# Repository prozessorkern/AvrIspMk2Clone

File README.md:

# Development Tools
In this repo there will be some development tools that can be used to work on some kind of hard and software projects...

## AvrIspMk2Clone
Clone of an AvrIspMk2 based on the work of http://www.ullihome.de/wiki/USBAVRLab/index

## jtagTc2050Adaptor
Adaptor PCB to connect a Tag Connect TC2050 10 Pin Needle adaptor to a standard 20 Pin JTAG Debugger
There are some additional tools integrated like a USB-UART Converter which can be connected to the TC2050 by setting Jumpers...

## pcbList
A Listing of all of my designed pcbs to find the data of a pcb a little bit faster...

## storageSolutions
Here are some sources to build systems to help storing and using components

### smdDispenser
This is something that I thought of to store and get my 0603 and 0805 smd parts (on smd rolls)
There are drawings you can use on a CNC machine... (wood, plastic and aluminium)
In addition you will need some Parts...

### smdStorage
Some drawings of inlays to store shorte SMD Strips 0603/0805 and bigger...

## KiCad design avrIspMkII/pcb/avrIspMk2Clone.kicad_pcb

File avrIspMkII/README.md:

# AvrIspMk2Clone
Clone of an AvrIspMk2 based on the work of http://www.ullihome.de/wiki/USBAVRLab/index

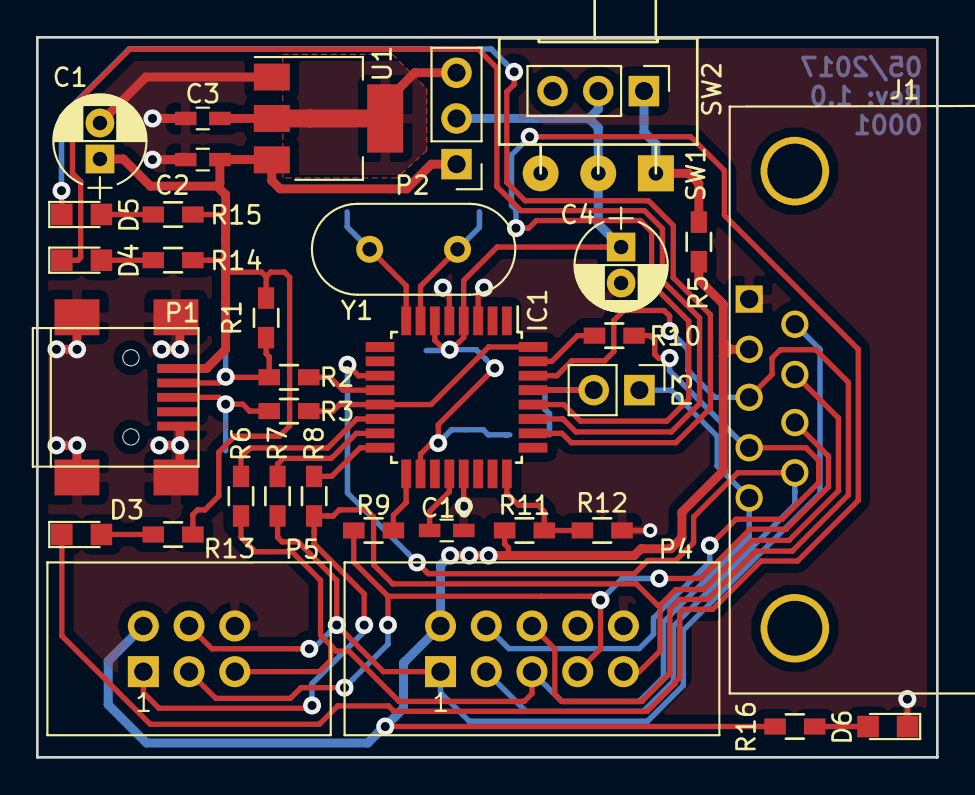
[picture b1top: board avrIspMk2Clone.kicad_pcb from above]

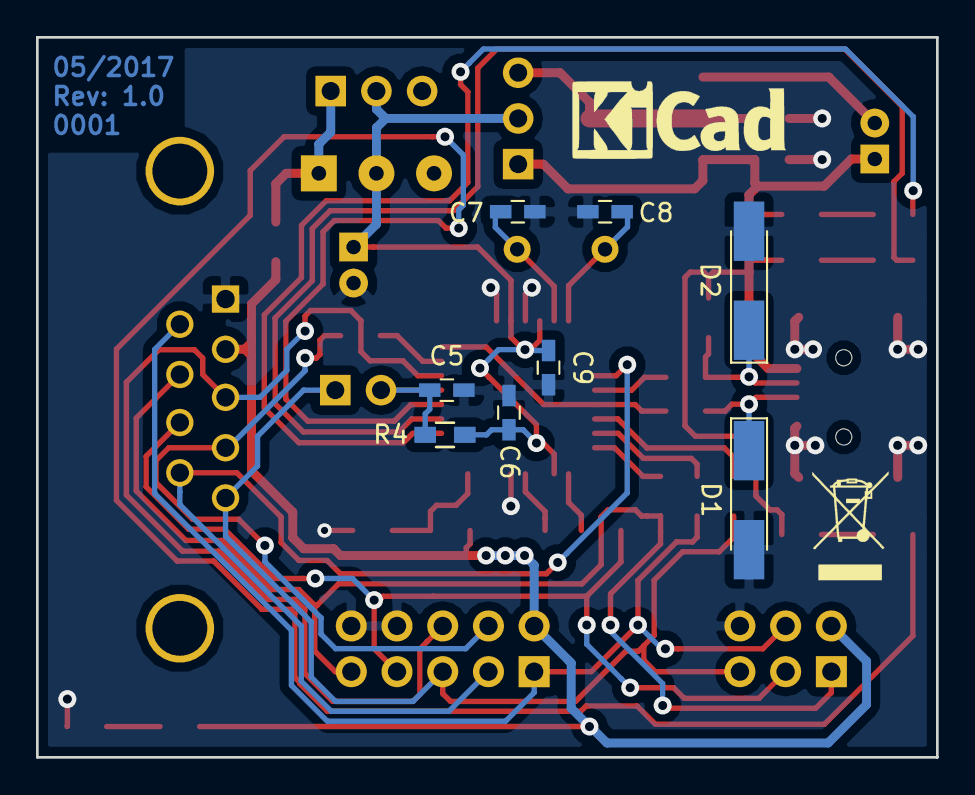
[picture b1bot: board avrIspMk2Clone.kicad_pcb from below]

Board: 2 copper layers, 50.0 x 40.0 mm, 43 parts (8 on the bottom side), 34 nets.

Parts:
C1, C4: 47u; CP_Radial_D5.0mm_P2.00mm
C2, C3, C5, C6, C9, C10: 100n; C_0603_HandSoldering
C7, C8: 22p; C_0603_HandSoldering
D1, D2: 3V3; D_MiniMELF_Handsoldering
D3, D6: BLUE; LED_0805
D4: RED; LED_0805
D5: GREEN; LED_0805
IC1: ATMEGA8-16AU; TQFP-32_7x7mm_Pitch0.8mm
J1: DB9; DB9FC
P1: USB_OTG; USB_Mini-B
P2: CONN_01X03; Pin_Header_Straight_1x03_Pitch2.54mm
P3: CONN_01X02; Pin_Header_Straight_1x02_Pitch2.54mm
P4: CONN_02X05; IDC_Header_Straight_10pins
P5: CONN_02X03; IDC_Header_Straight_6pins
R1: 2k2; R_0603_HandSoldering
R2, R3: 39; R_0603_HandSoldering
R4, R12: 10k; R_0603_HandSoldering
R5: 1; R_0603_HandSoldering
R6, R7, R8, R9: 100; R_0603_HandSoldering
R10, R13, R14, R15, R16: 1k; R_0603_HandSoldering
R11: 22k; R_0603_HandSoldering
SW1: SW_SPDT; SW_Micro_Slide_3.8
SW2: SW_SPDT; Pin_Header_Straight_1x03_Pitch2.54mm
U1: LM1117-3.3; SOT-223
Y1: 12MHz; Crystal_HC49-U_Vertical

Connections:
+3V3: C3.1, P2.3, U1.2, U1.4
+5V: C1.1, C2.1, P1.1, P2.1, R1.2, R13.2, R14.2, R15.2, U1.3
/AVREF: C10.1, IC1.20
/LED_BLUE: D3.1, IC1.28
/LED_GREEN: D5.1, IC1.26
/LED_RED: D4.1, IC1.27
/MEASURE: IC1.24, R11.1, R12.2
/MISO_OUT: J1.7, P4.9, P5.1, R8.2
/MOSI_OUT: J1.6, P4.1, P5.4, R7.2
/RESET: C5.1, IC1.29, P3.2, R4.1
/RESET_OUT: J1.5, P3.1, P4.5, P5.5, R6.2
/RXD_OUT: IC1.30, J1.3, P4.6
/SCK_OUT: J1.8, P4.7, P5.3, R9.2
/TXD_OUT: J1.4, P4.4, R10.1
/USB_D_+: IC1.13, IC1.32, R3.1
/USB_D_-: IC1.12, R2.1
/USIG1: IC1.11, J1.9, P4.3
/VCC_OUT: J1.2, P4.2, P5.2, R5.2, R11.2, R16.2
GND: C1.2, C2.2, C3.2, C4.2, C5.2, C6.2, C7.2, C8.2, C9.2, C10.2, D1.2, D2.2, D6.1, IC1.3, IC1.5, IC1.21, J1.1, P1.5, P1.6, P4.8, P4.10, P5.6, R12.1, U1.1
unnamed: C7.1, IC1.7, Y1.1
unnamed: C8.1, IC1.8, Y1.2
unnamed: D1.1, P1.3, R3.2
unnamed: D2.1, P1.2, R1.1, R2.2
unnamed: D3.2, R13.1
unnamed: D4.2, R14.1
unnamed: D5.2, R15.1
unnamed: D6.2, R16.1
unnamed: IC1.14, R6.1
unnamed: IC1.15, R7.1
unnamed: IC1.16, R8.1
unnamed: IC1.17, R9.1
unnamed: IC1.31, R10.2
unnamed: R5.1, SW1.1, SW2.1
VCC: C4.1, C6.1, C9.1, IC1.4, IC1.6, IC1.18, P2.2, R4.2, SW1.2, SW2.2

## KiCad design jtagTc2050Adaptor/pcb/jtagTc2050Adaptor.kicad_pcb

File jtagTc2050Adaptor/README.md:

# jtagTc2050Adaptor
Adaptor PCB to connect a Tag Connect TC2050 10 Pin Needle adaptor to a standard 20 Pin JTAG Debugger
There are some additional tools integrated like a USB-UART Converter which can be connected to the TC2050 by setting Jumpers...

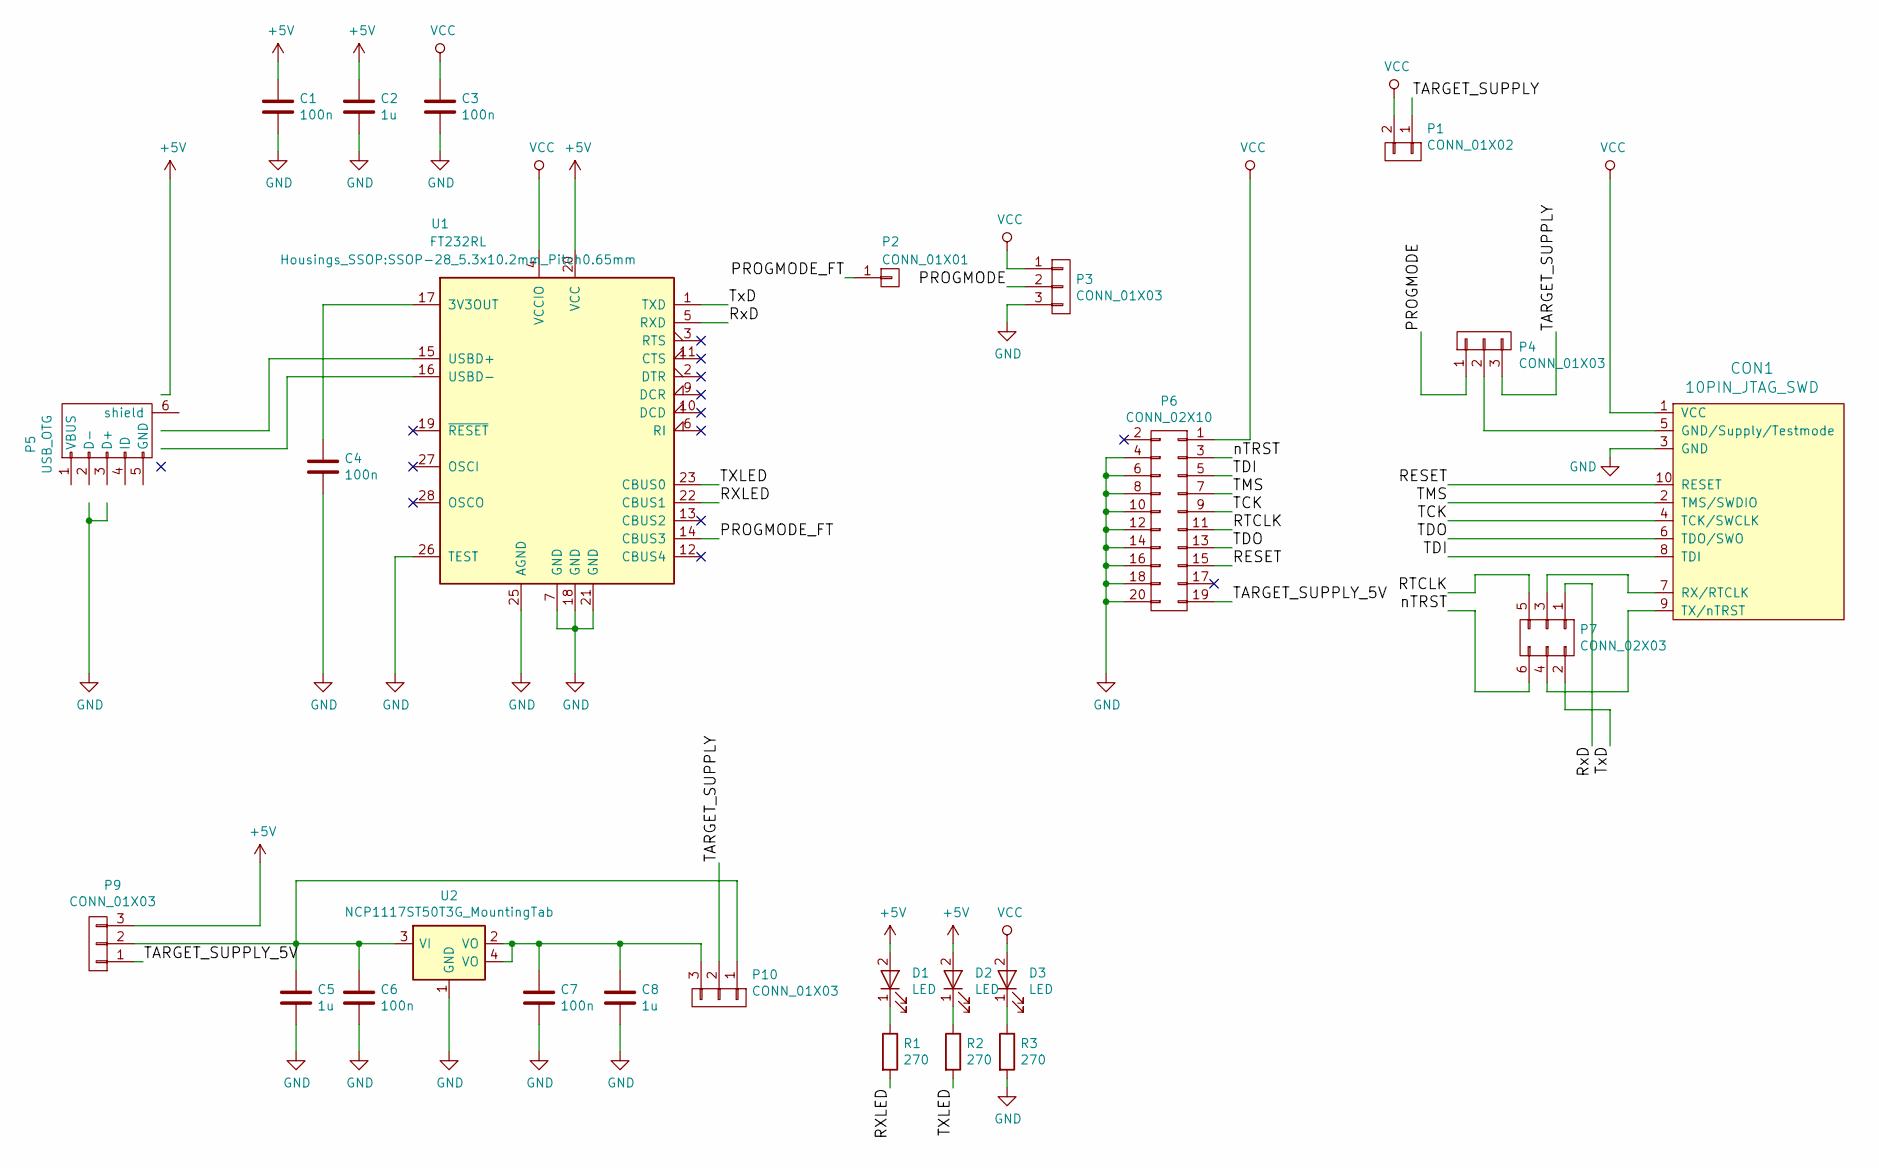
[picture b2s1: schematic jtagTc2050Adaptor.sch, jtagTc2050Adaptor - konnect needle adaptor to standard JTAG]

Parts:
C1, C3, C4, C6, C7: 100n; C_0603_HandSoldering
C2, C5, C8: 1u; C_0603_HandSoldering
CON1: 10PIN_JTAG_SWD; IDC_Header_Straight_10pins
D1, D2, D3: LED; LED_0805
P1: CONN_01X02; Pin_Header_Straight_1x02_Pitch2.54mm
P2: CONN_01X01; Pin_Header_Straight_1x01_Pitch2.54mm
P3, P4, P9, P10: CONN_01X03; Pin_Header_Straight_1x03_Pitch2.54mm
P5: USB_OTG; USB_Mini-B
P6: CONN_02X10; IDC_Header_Straight_20pins
P7: CONN_02X03; Pin_Header_Straight_2x03_Pitch2.54mm
R1, R2, R3: 270; R_0603_HandSoldering
U1: FT232RL; SSOP-28_5.3x10.2mm_Pitch0.65mm
U2: NCP1117ST50T3G_MountingTab; SOT-223

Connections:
+5V: C1.1, C2.1, D1.2 (A), D2.2 (A), P5.1 (VBUS), P9.3, U1.20 (VCC)
/PROGMODE: P3.2, P4.1
/PROGMODE_FT: P2.1, U1.14 (CBUS3)
/RESET: CON1.10 (RESET), P6.15
/RTCLK: P6.11, P7.5
/RXLED: R1.2, U1.22 (CBUS1)
/RxD: P7.1, U1.5 (RXD)
/TARGET_SUPPLY: P1.1, P4.3, P10.2
/TARGET_SUPPLY_5V: P6.19, P9.1
/TCK: CON1.4 (TCK/SWCLK), P6.9
/TDI: CON1.8 (TDI), P6.5
/TDO: CON1.6 (TDO/SWO), P6.13
/TMS: CON1.2 (TMS/SWDIO), P6.7
/TXLED: R2.2, U1.23 (CBUS0)
/TxD: P7.2, U1.1 (TXD)
/nTRST: P6.3, P7.6
GND: C1.2, C2.2, C3.2, C4.2, C5.2, C6.2, C7.2, C8.2, CON1.3 (GND), P3.3, P5.5 (GND), P5.6 (shield), P6.4, P6.6, P6.8, P6.10, P6.12, P6.14, P6.16, P6.18, P6.20, R3.2, U1.7 (GND), U1.18 (GND), U1.21 (GND), U1.25 (AGND), U1.26 (TEST), U2.1 (GND)
unnamed: C4.1, U1.17 (3V3OUT)
unnamed: C5.1, C6.1, P9.2, P10.1, U2.3 (VI)
unnamed: C7.1, C8.1, P10.3, U2.2 (VO), U2.4 (VO)
unnamed: CON1.5 (GND/Supply/Testmode), P4.2
unnamed: CON1.7 (RX/RTCLK), P7.3
unnamed: CON1.9 (TX/nTRST), P7.4
unnamed: D1.1 (K), R1.1
unnamed: D2.1 (K), R2.1
unnamed: D3.1 (K), R3.1
unnamed: P5.2 (D-), U1.16 (USBD-)
unnamed: P5.3 (D+), U1.15 (USBD+)
VCC: C3.1, CON1.1 (VCC), D3.2 (A), P1.2, P3.1, P6.1, U1.4 (VCCIO)

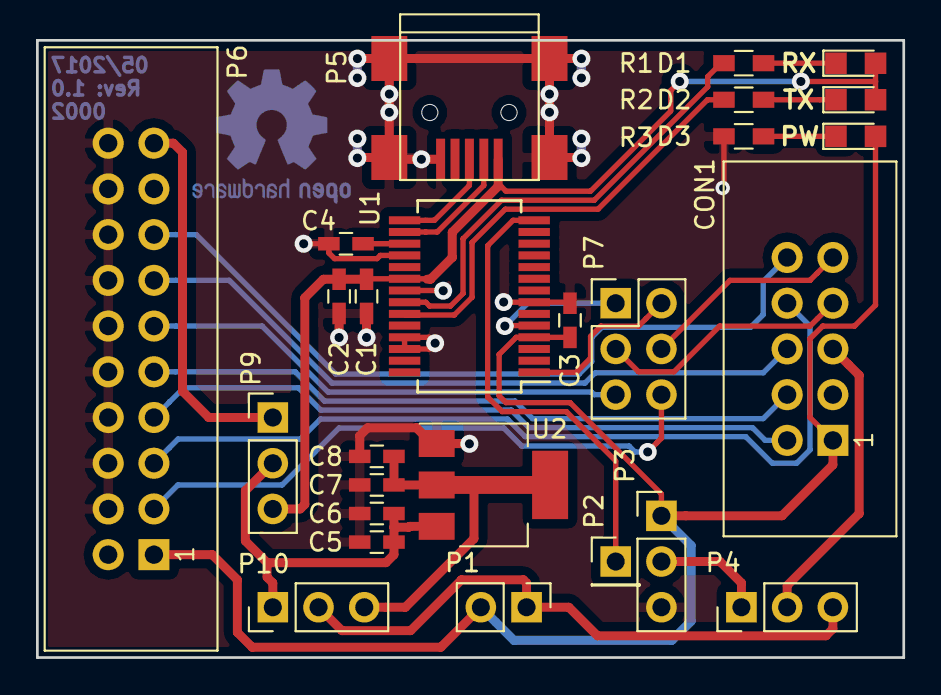
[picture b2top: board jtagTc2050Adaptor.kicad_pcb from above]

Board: 2 copper layers, 48.1 x 34.3 mm, 26 parts (0 on the bottom side), 29 nets.

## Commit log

2017-02-05 finished layout - maybe some improvements to do ;)
2017-02-12 Changed the Slide Switch to a Model from Pollin
2017-02-12 changed resistors and caps from 0805 to 0603
2017-03-14 Changed the purpose of the repo to hold more than one development tool...
    From now on the single tools will be kept in subdirectories.
2017-03-14 Readme Syntax...
2017-03-28 added a adaptor board from 20pin JTAG to 10 pin TC2050 Header with FT232RL Chip for special purpose
2017-03-30 finished jtagTc2050Adaptor Layout
2017-04-15 Added two projects to store your SMD components...
2017-04-15 LICENSE file added...
2017-04-23 finished layout for avrIspMk2Clone
    generated documentation and gerber files
2017-04-29 changed symbol to new library (usb otg)
2017-05-13 finished some layouts
    added pcb numbering and revision
    added a pcb list
    orderes the pcbs
2019-08-27 added some new pcbs to the pcblist
2020-09-04 added arty sniff
